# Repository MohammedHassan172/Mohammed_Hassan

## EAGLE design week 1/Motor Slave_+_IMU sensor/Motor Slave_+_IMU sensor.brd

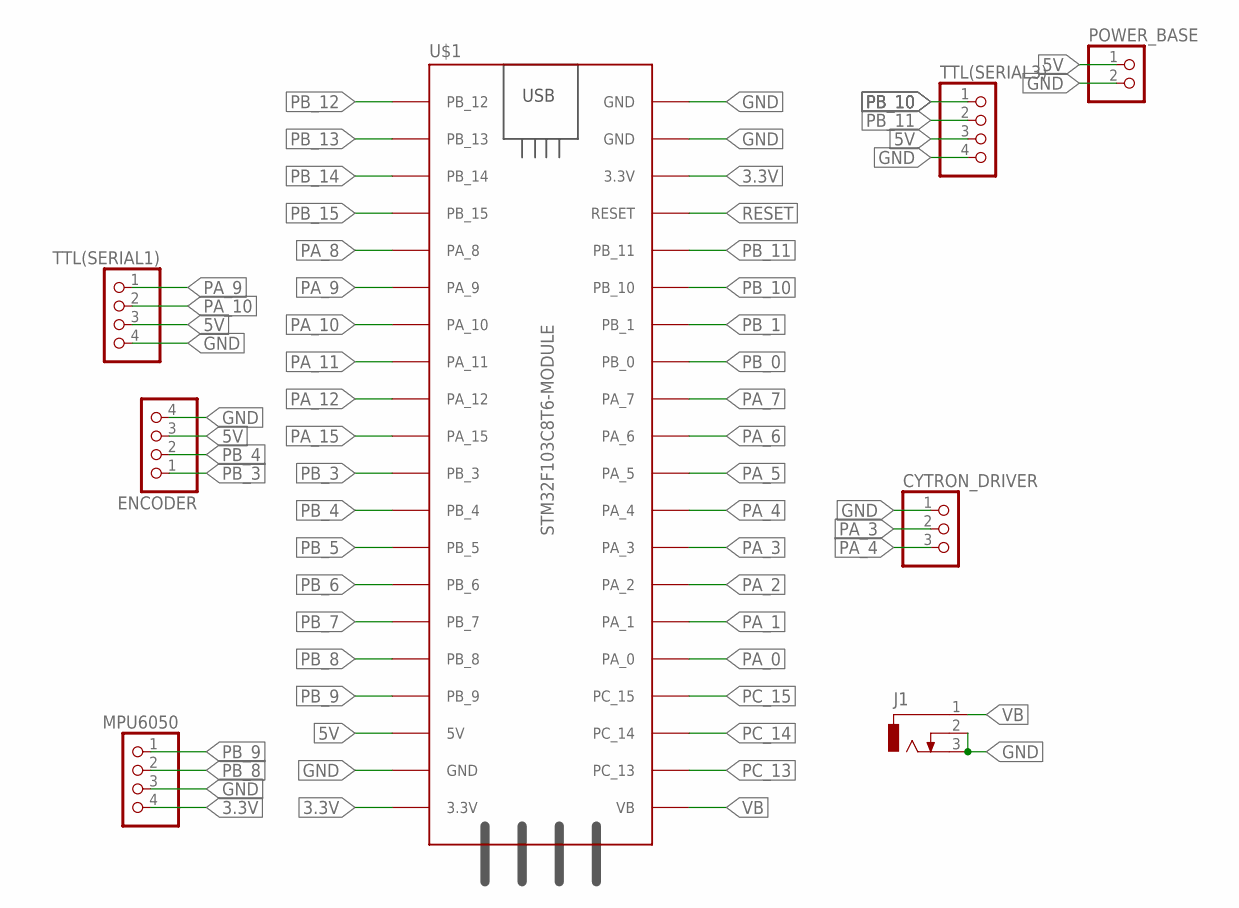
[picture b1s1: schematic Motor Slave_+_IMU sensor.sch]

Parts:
CYTRON_DRIVER: PINHD-3_DATA; 1X03_DATA
ENCODER: PINHD-4_DATA; 1X04_DATA
J1: CON_JACK; DCJ0303
MPU6050: PINHD-4_DATA; 1X04_DATA
POWER_BASE: PINHD-2_DATA; 1X02_DATA
TTL(SERIAL1), TTL(SERIAL3): PINHD-4_DATA; 1X04_DATA
U$1: STM32F103C8T6-MODULE

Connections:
3.3V: MPU6050.4, U$1.3.3V_1 (3.3V), U$1.3.3V_2 (3.3V)
5V: ENCODER.3, POWER_BASE.1, TTL(SERIAL1).3, TTL(SERIAL3).3, U$1.5V
GND: CYTRON_DRIVER.1, ENCODER.4, J1.2, J1.3, MPU6050.3, POWER_BASE.2, TTL(SERIAL1).4, TTL(SERIAL3).4, U$1.GND_1 (GND), U$1.GND_2 (GND), U$1.GND_3 (GND)
PA_0: U$1.PA_0
PA_1: U$1.PA_1
PA_2: U$1.PA_2
PA_3: CYTRON_DRIVER.2, U$1.PA_3
PA_4: CYTRON_DRIVER.3, U$1.PA_4
PA_5: U$1.PA_5
PA_6: U$1.PA_6
PA_7: U$1.PA_7
PA_8: U$1.PA_8
PA_9: TTL(SERIAL1).1, U$1.PA_9
PA_10: TTL(SERIAL1).2, U$1.PA_10
PA_11: U$1.PA_11
PA_12: U$1.PA_12
PA_15: U$1.PA_15
PB_0: U$1.PB_0
PB_1: U$1.PB_1
PB_3: ENCODER.1, U$1.PB_3
PB_4: ENCODER.2, U$1.PB_4
PB_5: U$1.PB_5
PB_6: U$1.PB_6
PB_7: U$1.PB_7
PB_8: MPU6050.2, U$1.PB_8
PB_9: MPU6050.1, U$1.PB_9
PB_10: TTL(SERIAL3).1, U$1.PB_10
PB_11: TTL(SERIAL3).2, U$1.PB_11
PB_12: U$1.PB_12
PB_13: U$1.PB_13
PB_14: U$1.PB_14
PB_15: U$1.PB_15
PC_13: U$1.PC_13
PC_14: U$1.PC_14
PC_15: U$1.PC_15
RESET: U$1.RESET
VB: J1.1, U$1.VB

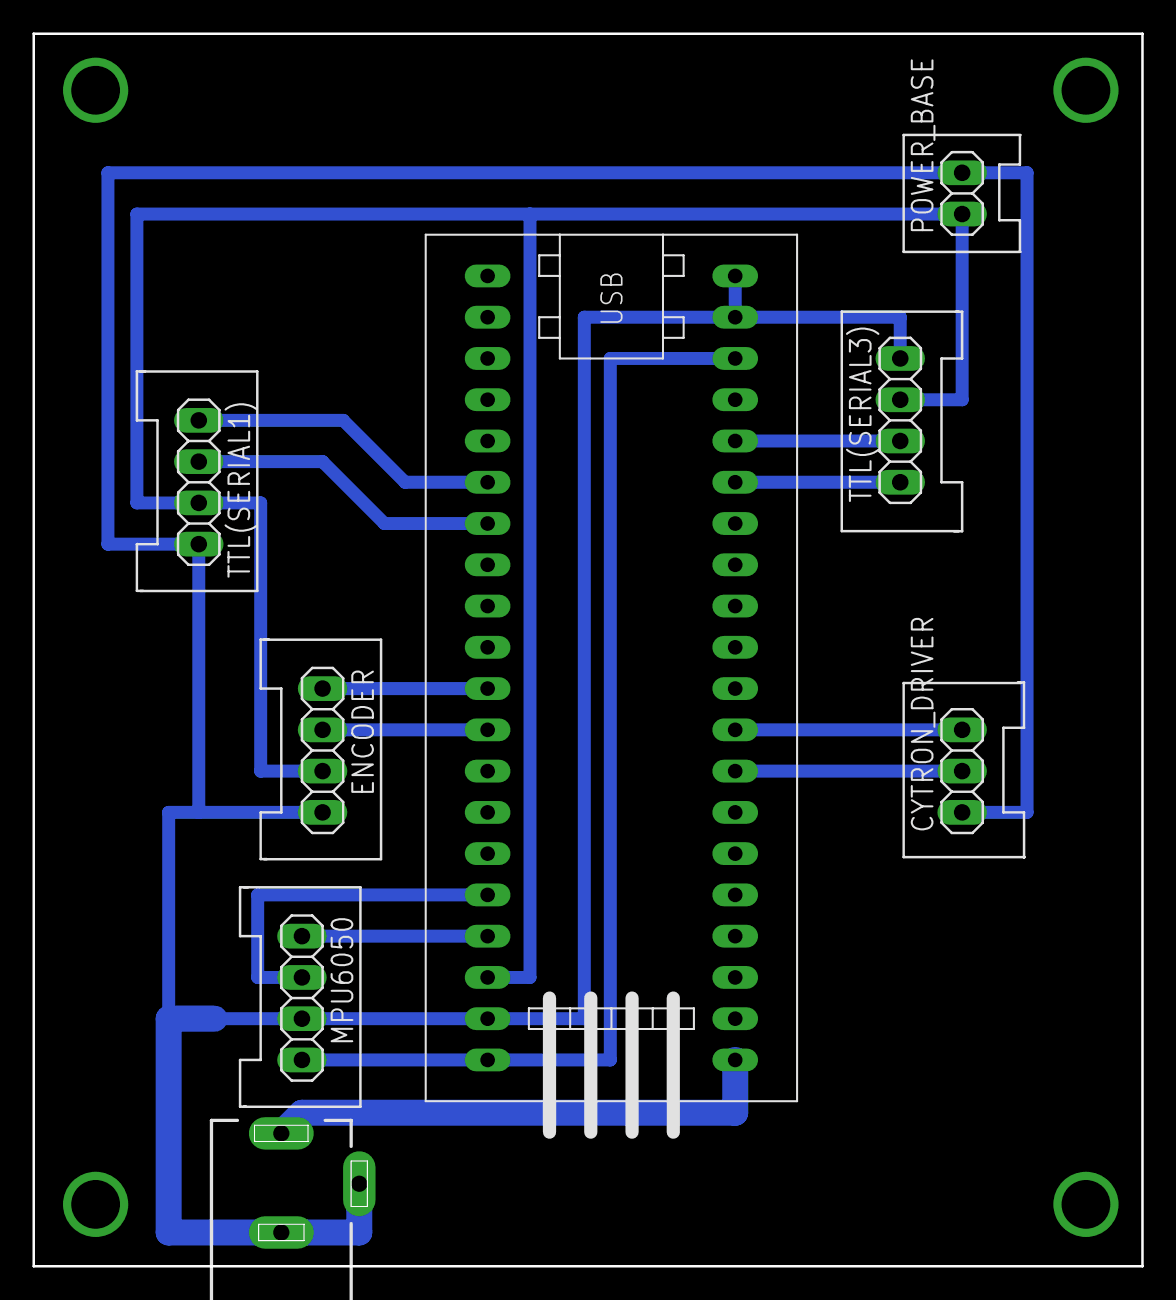
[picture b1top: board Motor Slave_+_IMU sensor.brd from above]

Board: 2 copper layers, 68.2 x 75.9 mm, 8 parts (0 on the bottom side), 14 nets.

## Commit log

2021-10-28 board design
2021-11-08 test
2021-11-09 added motor pins.
2021-11-16 lauch file
